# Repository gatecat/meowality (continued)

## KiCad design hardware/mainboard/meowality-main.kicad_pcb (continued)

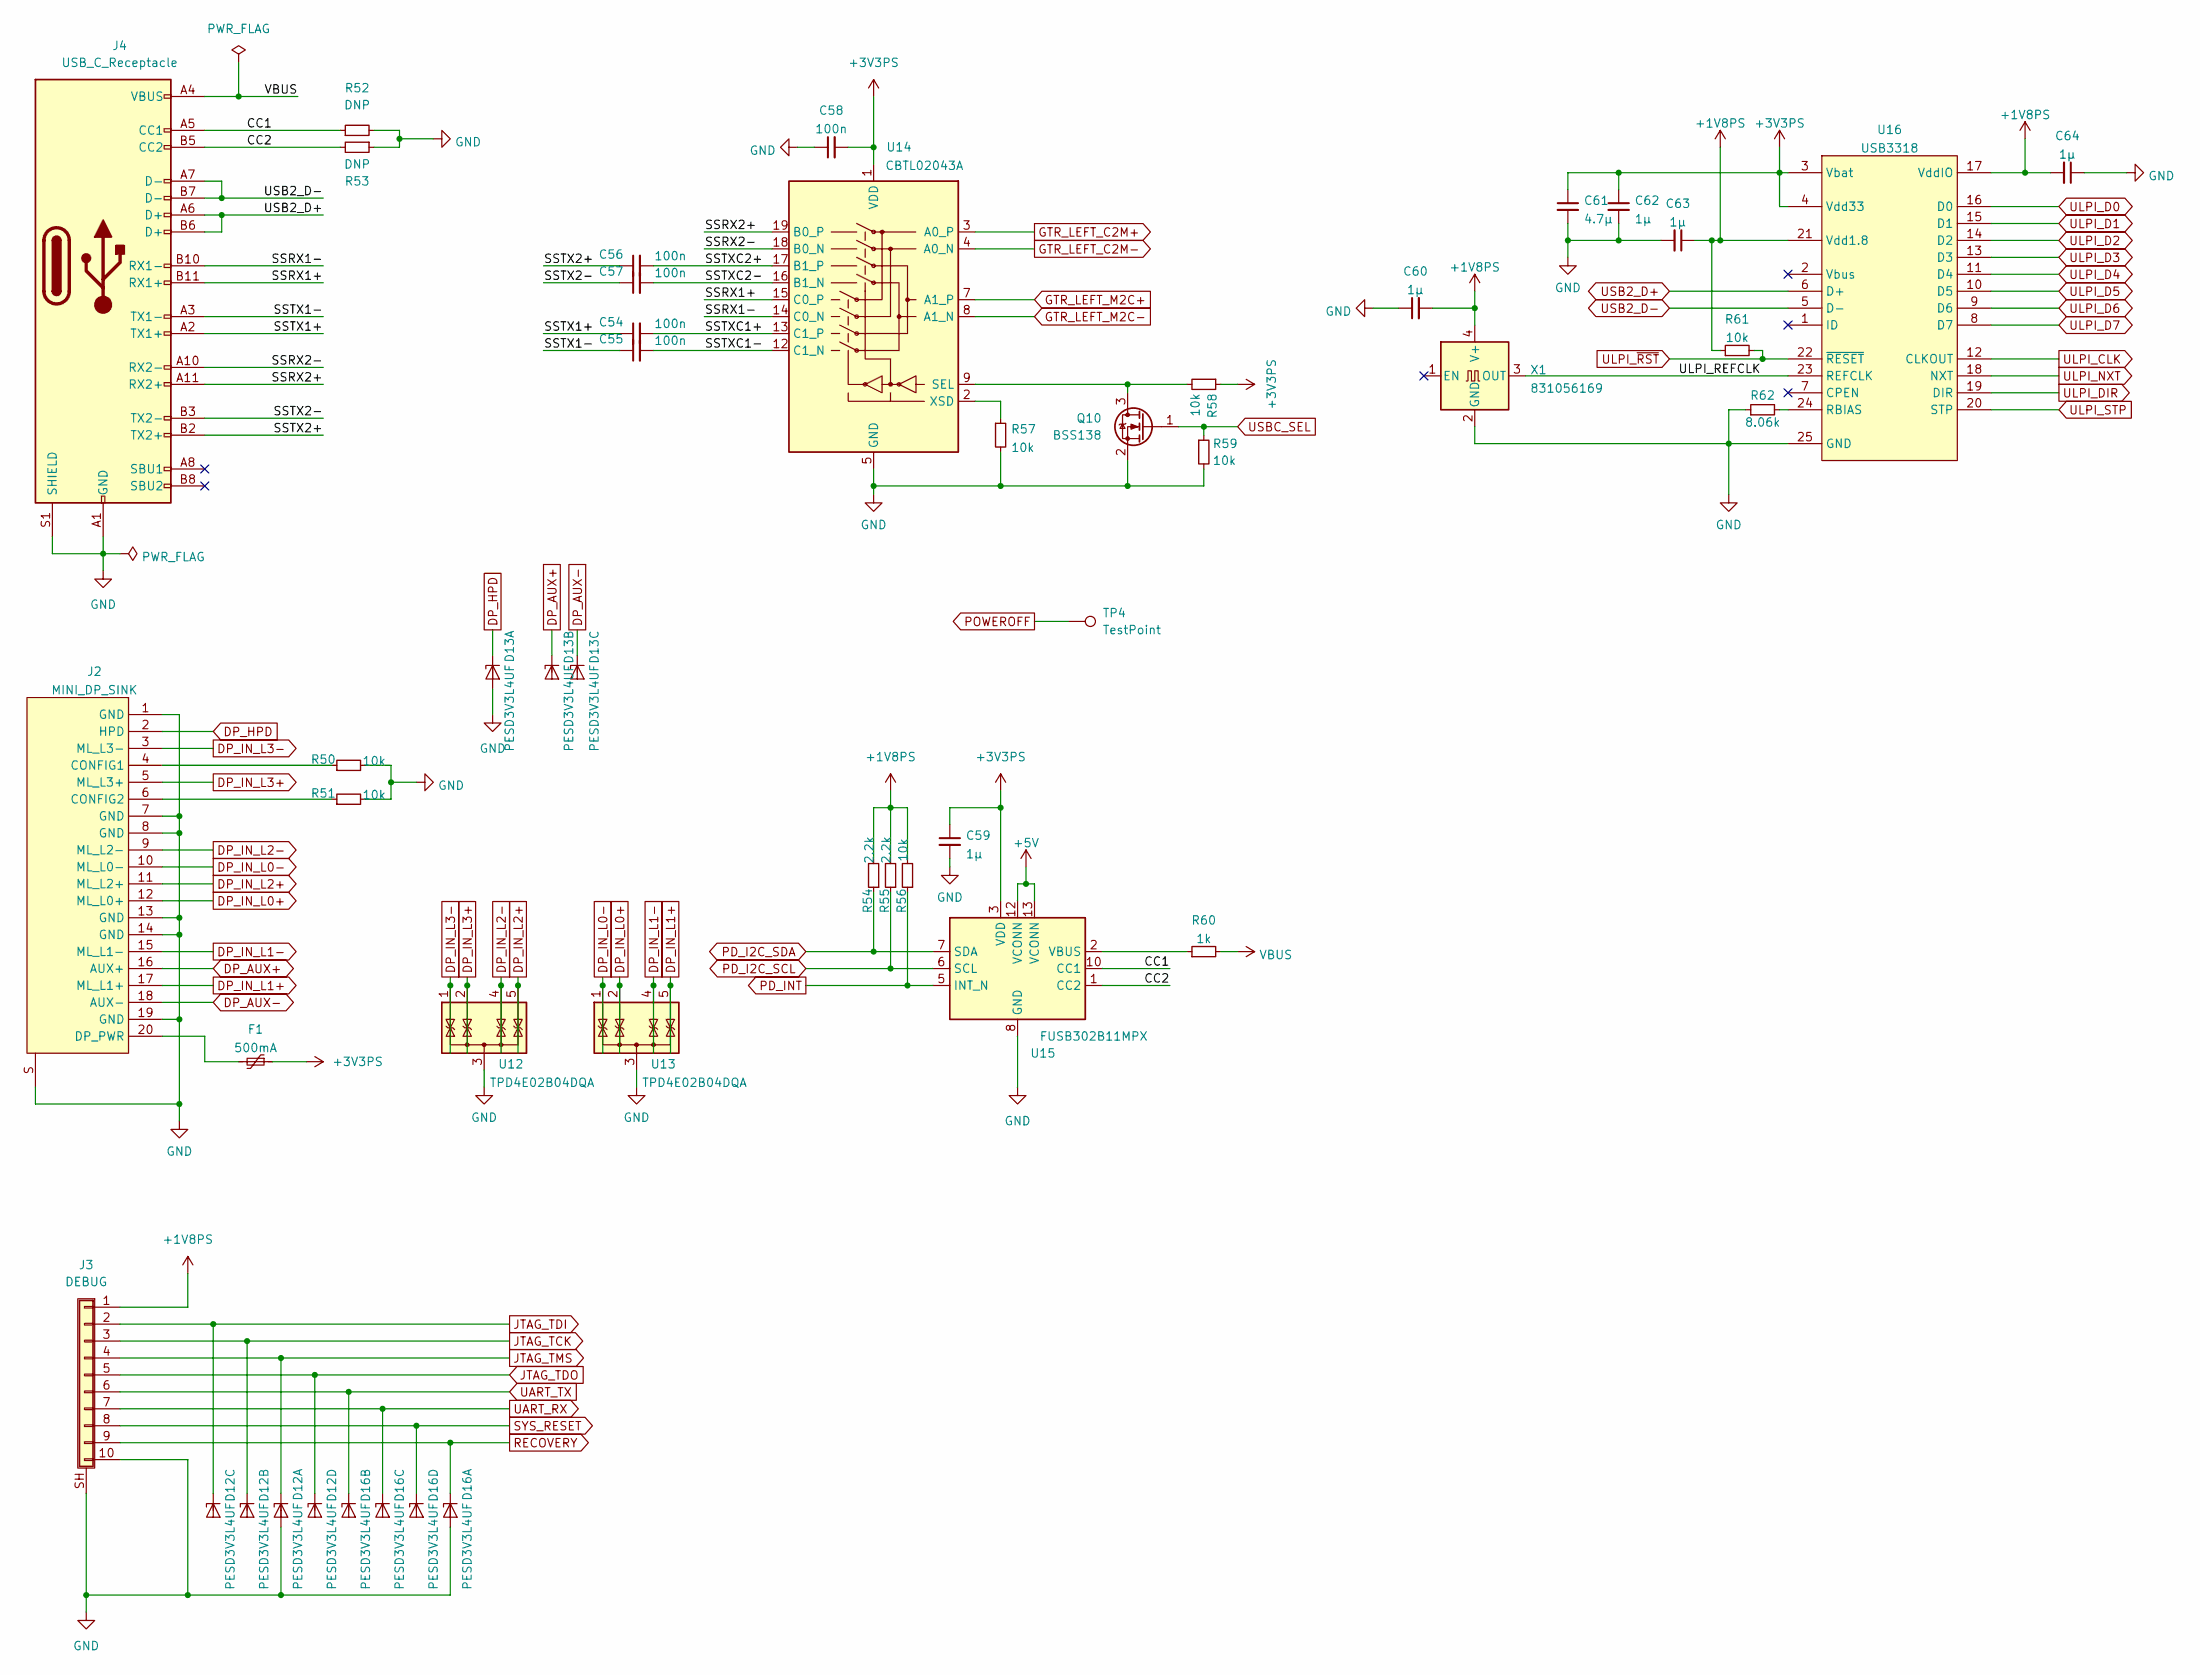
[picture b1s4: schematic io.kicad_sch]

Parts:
C54, C55, C56, C57, C58: 100n; C_0402_1005Metric
C59, C60, C62, C63, C64: 1µ; C_0603_1608Metric
C61: 4.7µ; C_0805_2012Metric
D12, D13, D16: PESD3V3L4UF; SOT-886
F1: 500mA; Fuse_0805_2012Metric
J2: MINI_DP_SINK; 2129320-3
J3: DEBUG; HARTING_10B1_JACK_AH
J4: USB_C_Receptacle; USB_C_Receptacle_Amphenol_12401610E4-2A
Q10: BSS138; SOT-23
R50, R51, R56, R57, R58, R59, R61: 10k; R_0402_1005Metric
R52, R53: DNP; R_0402_1005Metric
R54, R55: 2.2k; R_0402_1005Metric
R60: 1k; R_0402_1005Metric
R62: 8.06k; R_0402_1005Metric
TP4: TestPoint; TestPoint_Pad_D2.0mm
U12, U13: TPD4E02B04DQA; USON-10_2.5x1.0mm_P0.5mm
U14: CBTL02043A; WQFN-20-1EP_2.5x4.5mm_P0.5mm_EP1x2.9mm
U15: FUSB302B11MPX; WQFN-14-1EP_2.5x2.5mm_P0.5mm_EP1.45x1.45mm
U16: USB3318; HVQFN-24-1EP_4x4mm_P0.5mm_EP2.5x2.5mm
X1: 831056169; Oscillator_SMD_EuroQuartz_XO32-4Pin_3.2x2.5mm

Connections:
+1V8PS: C60.2, C63.1, C64.2, J3.1, R54.2, R55.2, R56.2, R61.1, U16.17 (VddIO), U16.21 (Vdd1.8), X1.4 (V+); also elsewhere on the board
+3V3PS: C58.2, C59.1, C61.1, C62.1, F1.1, R58.1, U14.1 (VDD), U14.6 (VDD), U14.10 (VDD), U15.3 (VDD), U15.4 (VDD), U16.3 (Vbat), U16.4 (Vdd33); also elsewhere on the board
+5V: U15.12 (VCONN), U15.13 (VCONN); also elsewhere on the board
/IO/CC1: J4.A5 (CC1), R52.1, U15.10 (CC1), U15.11 (CC1)
/IO/CC2: J4.B5 (CC2), R53.2, U15.1 (CC2), U15.14 (CC2)
/IO/SSRX1+: J4.B11 (RX1+), U14.15 (C0_P)
/IO/SSRX1-: J4.B10 (RX1-), U14.14 (C0_N)
/IO/SSRX2+: J4.A11 (RX2+), U14.19 (B0_P)
/IO/SSRX2-: J4.A10 (RX2-), U14.18 (B0_N)
/IO/SSTX1+: C54.1, J4.A2 (TX1+)
/IO/SSTX1-: C55.1, J4.A3 (TX1-)
/IO/SSTX2+: C56.1, J4.B2 (TX2+)
/IO/SSTX2-: C57.1, J4.B3 (TX2-)
/IO/SSTXC1+: C54.2, U14.13 (C1_P)
/IO/SSTXC1-: C55.2, U14.12 (C1_N)
/IO/SSTXC2+: C56.2, U14.17 (B1_P)
/IO/SSTXC2-: C57.2, U14.16 (B1_N)
/IO/ULPI_REFCLK: U16.23 (REFCLK), X1.3 (OUT)
DP_AUX+: D13.3 (K2), J2.16 (AUX+); also elsewhere on the board
DP_AUX-: D13.4 (K3), J2.18 (AUX-); also elsewhere on the board
DP_HPD: D13.1 (K1), J2.2 (HPD); also elsewhere on the board
DP_IN_L0+: J2.12 (ML_L0+), U13.2 (IO2), U13.9 (NC); also elsewhere on the board
DP_IN_L0-: J2.10 (ML_L0-), U13.1 (IO1), U13.10 (NC); also elsewhere on the board
DP_IN_L1+: J2.17 (ML_L1+), U13.5 (IO4), U13.6 (NC); also elsewhere on the board
DP_IN_L1-: J2.15 (ML_L1-), U13.4 (IO3), U13.7 (NC); also elsewhere on the board
DP_IN_L2+: J2.11 (ML_L2+), U12.5 (IO4), U12.6 (NC); also elsewhere on the board
DP_IN_L2-: J2.9 (ML_L2-), U12.4 (IO3), U12.7 (NC); also elsewhere on the board
DP_IN_L3+: J2.5 (ML_L3+), U12.2 (IO2), U12.9 (NC); also elsewhere on the board
DP_IN_L3-: J2.3 (ML_L3-), U12.1 (IO1), U12.10 (NC); also elsewhere on the board
GND: C58.1, C59.2, C60.1, C61.2, C62.2, C63.2, C64.1, D12.2 (A), D12.5 (A), D13.2 (A), D13.5 (A), D16.2 (A), D16.5 (A), J2.1 (GND), J2.7 (GND), J2.8 (GND), J2.13 (GND), J2.14 (GND), J2.19 (GND), J2.S, J3.10, J3.SH (Shield), J4.A1 (GND), J4.A12 (GND), J4.B1 (GND), J4.B12 (GND), J4.S1 (SHIELD), Q10.2 (S), R50.2, R51.2, R52.2, R53.1, R57.2, R59.2, R62.1, U12.3 (G), U12.8 (G), U13.3 (G), U13.8 (G), U14.5 (GND), U14.11 (GND), U14.20 (GND), U14.21 (GND), U15.8 (GND), U15.9 (GND), U15.15 (GND), U16.25 (GND), X1.2 (GND); also elsewhere on the board
GTR_LEFT_C2M+: U14.3 (A0_P); also elsewhere on the board
GTR_LEFT_C2M-: U14.4 (A0_N); also elsewhere on the board
GTR_LEFT_M2C+: U14.7 (A1_P); also elsewhere on the board
GTR_LEFT_M2C-: U14.8 (A1_N); also elsewhere on the board
JTAG_TCK: D12.3 (K2), J3.3; also elsewhere on the board
JTAG_TDI: D12.4 (K3), J3.2; also elsewhere on the board
JTAG_TDO: D12.6 (K4), J3.5; also elsewhere on the board
JTAG_TMS: D12.1 (K1), J3.4; also elsewhere on the board
unnamed: F1.2, J2.20 (DP_PWR)
unnamed: J2.4 (CONFIG1), R50.1
unnamed: J2.6 (CONFIG2), R51.1
unnamed: Q10.3 (D), R58.2, U14.9 (SEL)
unnamed: R57.1, U14.2 (XSD)
unnamed: R60.1, U15.2 (VBUS)
unnamed: R62.2, U16.24 (RBIAS)
PD_I2C_SCL: R55.1, U15.6 (SCL); also elsewhere on the board
PD_I2C_SDA: R54.1, U15.7 (SDA); also elsewhere on the board
PD_INT: R56.1, U15.5 (INT_N); also elsewhere on the board
POWEROFF: TP4.1; also elsewhere on the board
RECOVERY: D16.1 (K1), J3.9; also elsewhere on the board
SYS_RESET: D16.6 (K4), J3.8; also elsewhere on the board
UART_RX: D16.4 (K3), J3.7; also elsewhere on the board
UART_TX: D16.3 (K2), J3.6; also elsewhere on the board
ULPI_CLK: U16.12 (CLKOUT); also elsewhere on the board
ULPI_D0: U16.16 (D0); also elsewhere on the board
ULPI_D1: U16.15 (D1); also elsewhere on the board
ULPI_D2: U16.14 (D2); also elsewhere on the board
ULPI_D3: U16.13 (D3); also elsewhere on the board
ULPI_D4: U16.11 (D4); also elsewhere on the board
ULPI_D5: U16.10 (D5); also elsewhere on the board
ULPI_D6: U16.9 (D6); also elsewhere on the board
ULPI_D7: U16.8 (D7); also elsewhere on the board
ULPI_DIR: U16.19 (DIR); also elsewhere on the board
ULPI_NXT: U16.18 (NXT); also elsewhere on the board
ULPI_STP: U16.20 (STP); also elsewhere on the board
ULPI_~RST: R61.2, U16.22 (~RESET); also elsewhere on the board
USB2_D+: J4.A6 (D+), J4.B6 (D+), U16.6 (D+)
USB2_D-: J4.A7 (D-), J4.B7 (D-), U16.5 (D-)
USBC_SEL: Q10.1 (G), R59.1; also elsewhere on the board
VBUS: J4.A4 (VBUS), J4.A9 (VBUS), J4.B4 (VBUS), J4.B9 (VBUS), R60.2; also elsewhere on the board

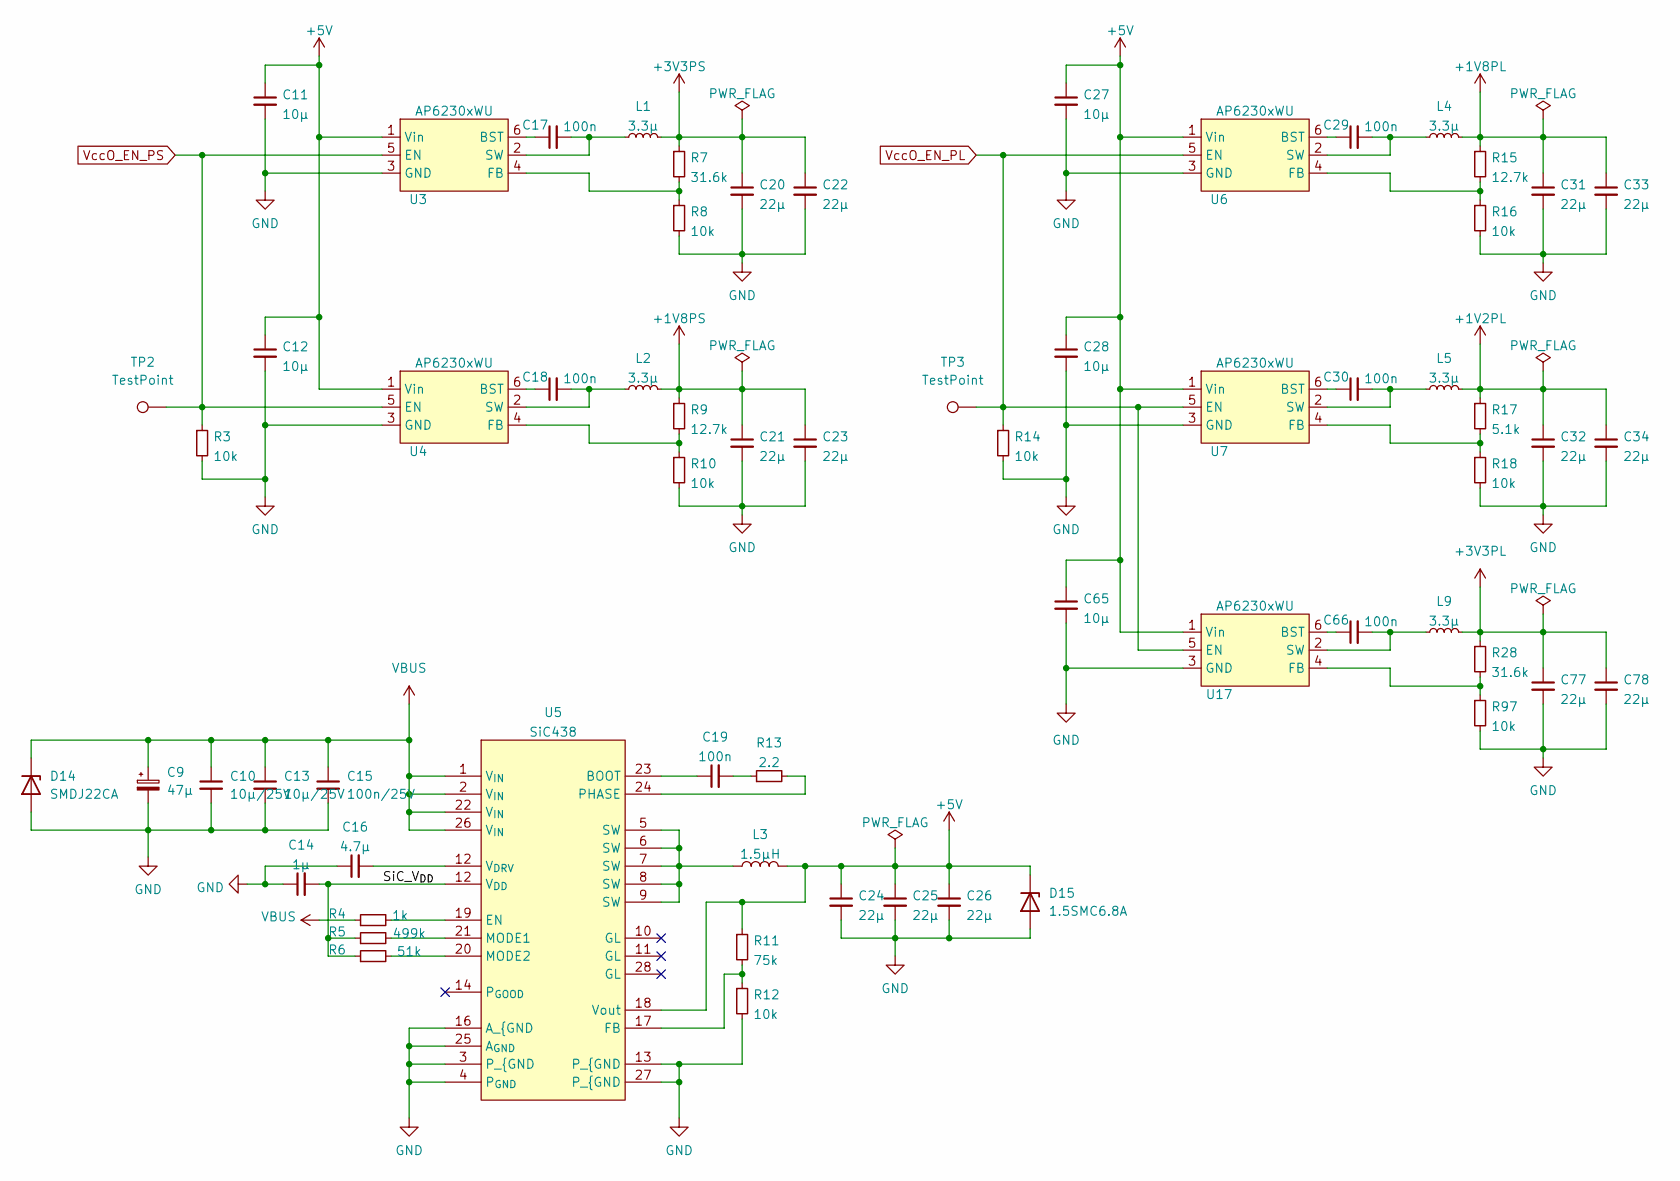
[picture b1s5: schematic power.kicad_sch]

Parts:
C9: 47µ; CP_Elec_6.3x3.9
C10, C13: 10µ/25V; C_1206_3216Metric
C11, C12, C27, C28, C65: 10µ; C_1206_3216Metric
C14: 1µ; C_0603_1608Metric
C15: 100n/25V; C_0805_2012Metric
C16: 4.7µ; C_0603_1608Metric
C17, C18, C19, C29, C30, C66: 100n; C_0402_1005Metric
C20, C21, C22, C23, C24, C25, C26, C31, C32, C33, C34, C77, C78: 22µ; C_1206_3216Metric
D14: SMDJ22CA; D_SMC
D15: 1.5SMC6.8A; D_SMC
L1, L2, L4, L5, L9: 3.3µ; BWVS00606045
L3: 1.5µH; L_Bourns_SRP7028A_7.3x6.6mm
R3, R8, R10, R12, R14, R16, R18, R97: 10k; R_0402_1005Metric
R4: 1k; R_0402_1005Metric
R5: 499k; R_0402_1005Metric
R6: 51k; R_0402_1005Metric
R7, R28: 31.6k; R_0402_1005Metric
R9, R15: 12.7k; R_0402_1005Metric
R11: 75k; R_0402_1005Metric
R13: 2.2; R_0402_1005Metric
R17: 5.1k; R_0402_1005Metric
TP2, TP3: TestPoint; TestPoint_Pad_D2.0mm
U3, U4, U6, U7, U17: AP6230xWU; TSOT-23-6
U5: SiC438; MLP44-24L

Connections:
+1V2PL: C32.1, C34.1, L5.2, R17.1; also elsewhere on the board
+1V8PL: C31.1, C33.1, L4.2, R15.1; also elsewhere on the board
+1V8PS: C21.1, C23.1, L2.2, R9.1; also elsewhere on the board
+3V3PL: C77.1, C78.1, L9.2, R28.1; also elsewhere on the board
+3V3PS: C20.1, C22.1, L1.2, R7.1; also elsewhere on the board
+5V: C11.1, C12.1, C24.1, C25.1, C26.1, C27.1, C28.1, C65.1, D15.1 (K), L3.2, R11.1, U3.1 (Vin), U4.1 (Vin), U5.18 (Vout), U6.1 (Vin), U7.1 (Vin), U17.1 (Vin); also elsewhere on the board
GND: C9.2, C10.2, C11.2, C12.2, C13.2, C14.1, C15.2, C16.1, C20.2, C21.2, C22.2, C23.2, C24.2, C25.2, C26.2, C27.2, C28.2, C31.2, C32.2, C33.2, C34.2, C65.2, C77.2, C78.2, D14.2 (A), D15.2 (A), R3.2, R8.2, R10.2, R12.2, R14.2, R16.2, R18.2, R97.2, U3.3 (GND), U4.3 (GND), U5.3 (P_{GND), U5.4 (P_{GND}), U5.13 (P_{GND), U5.16 (A_{GND), U5.25 (A_{GND}), U5.27 (P_{GND), U6.3 (GND), U7.3 (GND), U17.3 (GND); also elsewhere on the board
unnamed: C17.1, U3.6 (BST)
unnamed: C17.2, L1.1, U3.2 (SW)
unnamed: C18.1, U4.6 (BST)
unnamed: C18.2, L2.1, U4.2 (SW)
unnamed: C19.1, U5.23 (BOOT)
unnamed: C19.2, R13.1
unnamed: C29.1, U6.6 (BST)
unnamed: C29.2, L4.1, U6.2 (SW)
unnamed: C30.1, U7.6 (BST)
unnamed: C30.2, L5.1, U7.2 (SW)
unnamed: C66.1, U17.6 (BST)
unnamed: C66.2, L9.1, U17.2 (SW)
unnamed: L3.1, U5.5 (SW), U5.6 (SW), U5.7 (SW), U5.8 (SW), U5.9 (SW)
unnamed: R4.2, U5.19 (EN)
unnamed: R5.2, U5.21 (MODE1)
unnamed: R6.2, U5.20 (MODE2)
unnamed: R7.2, R8.1, U3.4 (FB)
unnamed: R9.2, R10.1, U4.4 (FB)
unnamed: R11.2, R12.1, U5.17 (FB)
unnamed: R13.2, U5.24 (PHASE)
unnamed: R15.2, R16.1, U6.4 (FB)
unnamed: R17.2, R18.1, U7.4 (FB)
unnamed: R28.2, R97.1, U17.4 (FB)
VBUS: C9.1, C10.1, C13.1, C15.1, D14.1 (K), R4.1, U5.1 (V_{IN}), U5.2 (V_{IN}), U5.22 (V_{IN}), U5.26 (V_{IN}); also elsewhere on the board
VccO_EN_PL: R14.1, TP3.1, U6.5 (EN), U7.5 (EN), U17.5 (EN); also elsewhere on the board
VccO_EN_PS: R3.1, TP2.1, U3.5 (EN), U4.5 (EN); also elsewhere on the board
